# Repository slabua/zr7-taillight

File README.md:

# ZR-7 ATtiny85 Tail Light

###### tags: `SLBLabs` `SLB Labs` `ZR-7` `ZR7` `ZR750` `Kawasaki` `KawasakiZR7` `TailLight` `TailLights` `ATtiny` `ATtiny85` `Arduino` `C/C++`

## A custom motorcycle tail light based on ATtiny85
> Hardware • Firmware • Animations • Automotive-grade considerations

---

## ✦ Overview

The **ZR-7 Tail Light** is a custom-designed motorcycle tail light built around the **ATtiny85** microcontroller.  
It spans the complete stack, from schematic and PCB design to low-level firmware and animation logic, with a focus on robustness, simplicity, and visual clarity.

The goal of this project is not only to function as a tail light, but to serve as a well-engineered embedded system suitable for real automotive environments.

---

## ✦ Features

- ATtiny85-based control logic
- Addressable RGB LED layout
- Distinct operating modes:
  - Tail / running light
  - Brake light
  - Left / right indicators
- Deterministic, non-blocking firmware
- Designed for 12 V motorcycle electrical systems
- Compact, purpose-built PCB

---

## ✦ Hardware

### Core Components

- **MCU:** ATtiny85
- **LEDs:** Addressable RGB LEDs
- **Power:** 12 V input with on-board regulation
- **Inputs:** Brake, left indicator, right indicator

### Design Notes

Several constraints influenced the hardware design:

- **Automotive signal noise**
  Input conditioning and pull-down strategies are used to avoid floating or unstable states.

- **Power integrity**
  The circuit is designed to tolerate voltage fluctuations typical of motorcycle electrical systems.

- **Mechanical constraints**
  PCB shape, connector placement, and LED layout are optimized for the tail light enclosure.

Schematics, PCB layouts, and manufacturing files are included in the `hardware/` directory.

---

## ✦ Firmware

Firmware is written in **C**, targeting the ATtiny85 directly, with no operating system or dynamic memory usage.

### Architecture Highlights

- **State-based rendering**
  Tail, brake, and indicator logic are resolved into a single rendering pipeline.

- **Time-driven animations**
  All animations are non-blocking and tick-based.

- **Config-ready architecture**
  The firmware structure allows future addition of persistent configuration if needed.

Firmware source is located in the `firmware/` directory.

---

## ✦ Build & Flashing

The firmware is developed and flashed using the **Arduino IDE** with an external ISP programmer.

### Requirements

- Arduino IDE
- ATtiny board core (e.g. **ATTinyCore** by Spence Konde)
- Adafruit_NeoPixel library
- ISP programmer:
  - USBtinyISP
  - USBasp

### Arduino IDE Setup

1. Install the ATtiny board package via the Boards Manager.
2. Install the Adafruit_NeoPixel library via the Library Manager.
2. Connect the ISP programmer to the ATtiny85 ISP header.
3. In the Arduino IDE, configure:
   - **Board:** ATtiny85
   - **Clock:** 16.5 MHz
   - **B.O.D Level:** 4.3v
   - **Programmer:** USBtinyISP or USBasp

### Flashing

Use:

``Sketch → Upload Using Programmer``

This compiles the firmware and flashes it directly to the ATtiny85.  
No bootloader is used.

---

## ✦ Media

### PCB details

<details>
  <summary>[More]</summary>

</details>

---

### PCB assembly

<details>
  <summary>[More]</summary>

</details>

---

### Diffuser

<details>
  <summary>[More]</summary>

</details>

---

### Relay

<details>
  <summary>[More]</summary>

</details>

---

- [TODO] Installed tail light images
- [TODO] Short animation demo videos

※ Attached photographs of the assembled PCB are representative of Rev 1.0.

---

## ✦ Repository Layout

```
zr7-taillight/
├── firmware/        # ATtiny85 firmware source
├── hardware/        # Schematics and PCB design
├── docs/            # Images and additional documentation
└── README.md
```

---

## ✦ Safety & Disclaimer

⚠️ **Important Notice**

This project is provided **as-is**, for educational and experimental purposes.

- The author makes **no guarantees** regarding road legality, safety compliance, or fitness for any particular vehicle.
- Modifying vehicle lighting may be regulated or restricted depending on jurisdiction.
- You are solely responsible for ensuring that any implementation complies with **local laws**, **vehicle regulations**, and **safety requirements**.

Use at your own risk.

---

## ✦ Sponsorship

This project is sponsored by **PCBWay**.

PCBWay provided support for PCB manufacturing during the prototyping and validation stages of this project.

It was my first time trying their services and I am pleased with the results.  
The order flow was a little different than what I was used to, but I have been diligently followed thorough the whole process.  
Other than PCB manufacturing, PCBWay also offers services such as CNC and 3D printing. Be sure to check them out at https://www.pcbway.com/

---

## ✦ License

Released under the **MIT License**.
See the `LICENSE` file for details.

---

## ✦ Project Status

The project is **functional and actively evolving**.
Both hardware and firmware are stable, with ongoing refinements and documentation improvements planned.

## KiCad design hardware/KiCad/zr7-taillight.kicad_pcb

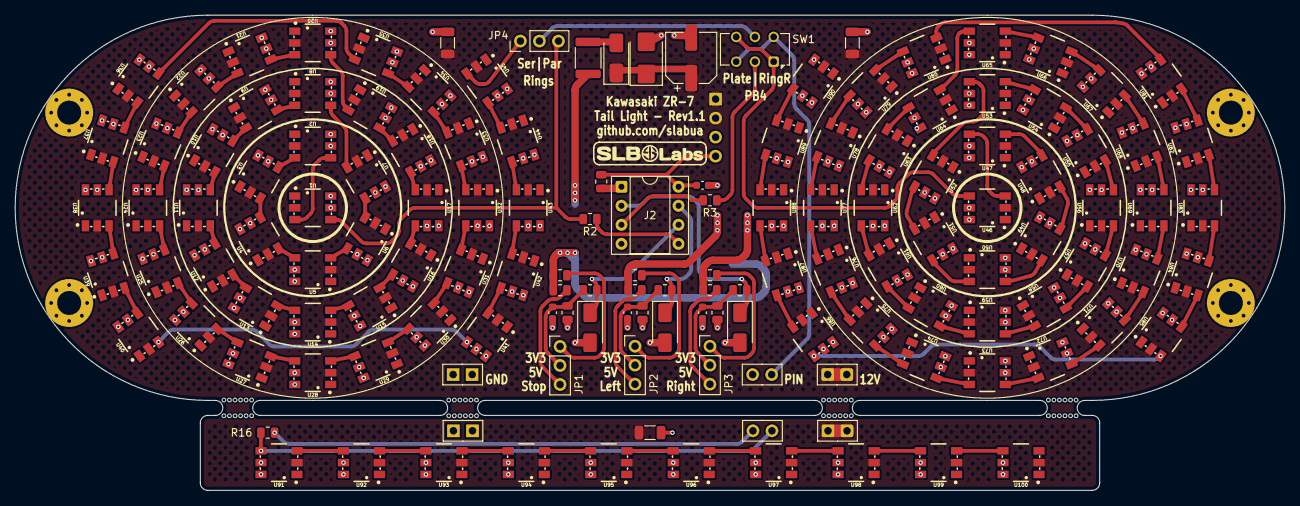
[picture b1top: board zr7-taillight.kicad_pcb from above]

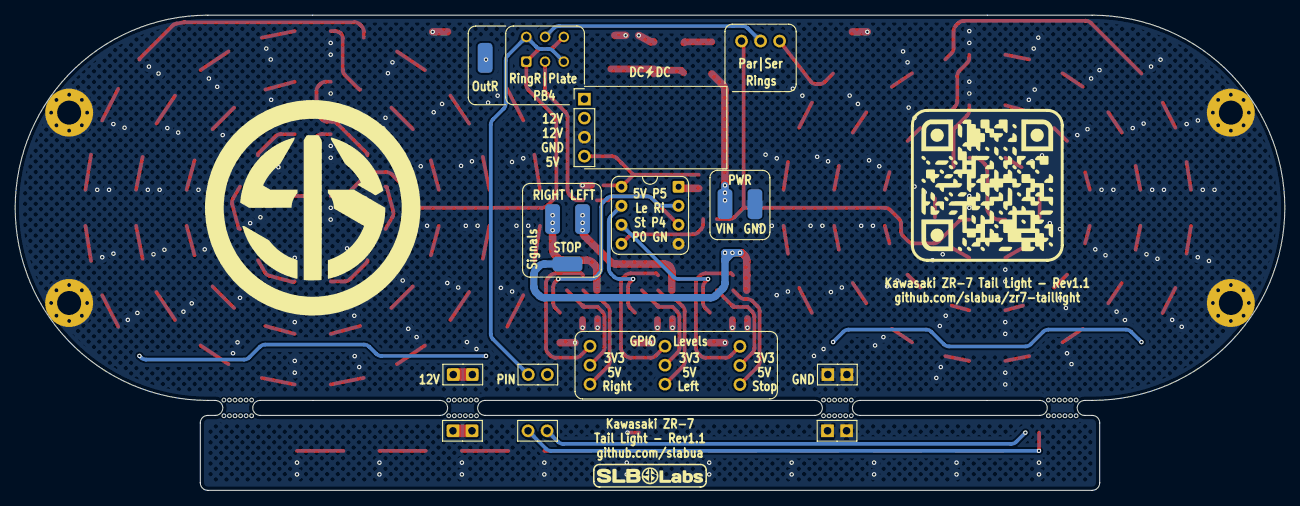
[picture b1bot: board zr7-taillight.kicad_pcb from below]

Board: 2 copper layers, 169.4 x 63.4 mm, 138 parts (2 on the bottom side), 125 nets.

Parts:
C1: 100u; CP_Elec_6.3x5.7
C2, C3, C4, C5: 100n; C_0603_1608Metric
C6, C7, C8: 1u; C_1206_3216Metric
D1: D_Schottky; D_SMA
D2: SMBJ14A; D_SMB
D3, D4, D5: SMAJ5.0A; D_SMA
F1: Polyfuse; SLB-Fuse_1812_4532Metric
J1: Conn_01x04_Pin; SLB-Mini_DCDC
J2: Conn_02x04_Counter_Clockwise; DIP-8_W7.62mm_Socket
JP1, JP2, JP3, JP4: Jumper_3_Open; PinHeader_1x03_P2.54mm_Vertical
R1: 10k; R_0805_2012Metric
R2, R3, R16: 330; R_0805_2012Metric
R4, R5, R6: 1k; R_0805_2012Metric
R7, R8, R9: 4k7; R_0805_2012Metric
R10, R11, R12: 22k; R_0805_2012Metric
R13, R14, R15: 39k; R_0805_2012Metric
Ref**: SLBLabs LOGO only w-border
SW1: SW_DPDT_x2; SW_CK_JS202011CQN_DPDT_Straight
U1, U2, U3, U4, U5, U6, U7, U8, U9, U10, U11, U12, U13, U14, U15, U16, U17, U18, U19, U20, U21, U22, U23, U24, U25, U26, U27, U28, U29, U30, U31, U32, U33, U34, U35, U36, U37, U38, U39, U40, U41, U42, U43, U44, U45, U46, U47, U48, U49, U50, U51, U52, U53, U54, U55, U56, U57, U58, U59, U60, U61, U62, U63, U64, U65, U66, U67, U68, U69, U70, U71, U72, U73, U74, U75, U76, U77, U78, U79, U80, U81, U82, U83, U84, U85, U86, U87, U88, U89, U90, U91, U92, U93, U94, U95, U96, U97, U98, U99, U100: WS2815; LED-TRICOLOR-5050

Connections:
5V: C2.1, J1.4, J2.8, R1.1
12V: C1.1, C6.1, C7.1, C8.1, D1.1 (K), D2.1 (A1), J1.1, J1.2, U1.2 (VDD), U2.2 (VDD), U3.2 (VDD), U4.2 (VDD), U5.2 (VDD), U6.2 (VDD), U7.2 (VDD), U8.2 (VDD), U9.2 (VDD), U10.2 (VDD), U11.2 (VDD), U12.2 (VDD), U13.2 (VDD), U14.2 (VDD), U15.2 (VDD), U16.2 (VDD), U17.2 (VDD), U18.2 (VDD), U19.2 (VDD), U20.2 (VDD), U21.2 (VDD), U22.2 (VDD), U23.2 (VDD), U24.2 (VDD), U25.2 (VDD), U26.2 (VDD), U27.2 (VDD), U28.2 (VDD), U29.2 (VDD), U30.2 (VDD), U31.2 (VDD), U32.2 (VDD), U33.2 (VDD), U34.2 (VDD), U35.2 (VDD), U36.2 (VDD), U37.2 (VDD), U38.2 (VDD), U39.2 (VDD), U40.2 (VDD), U41.2 (VDD), U42.2 (VDD), U43.2 (VDD), U44.2 (VDD), U45.2 (VDD), U46.2 (VDD), U47.2 (VDD), U48.2 (VDD), U49.2 (VDD), U50.2 (VDD), U51.2 (VDD), U52.2 (VDD), U53.2 (VDD), U54.2 (VDD), U55.2 (VDD), U56.2 (VDD), U57.2 (VDD), U58.2 (VDD), U59.2 (VDD), U60.2 (VDD), U61.2 (VDD), U62.2 (VDD), U63.2 (VDD), U64.2 (VDD), U65.2 (VDD), U66.2 (VDD), U67.2 (VDD), U68.2 (VDD), U69.2 (VDD), U70.2 (VDD), U71.2 (VDD), U72.2 (VDD), U73.2 (VDD), U74.2 (VDD), U75.2 (VDD), U76.2 (VDD), U77.2 (VDD), U78.2 (VDD), U79.2 (VDD), U80.2 (VDD), U81.2 (VDD), U82.2 (VDD), U83.2 (VDD), U84.2 (VDD), U85.2 (VDD), U86.2 (VDD), U87.2 (VDD), U88.2 (VDD), U89.2 (VDD), U90.2 (VDD), U91.2 (VDD), U92.2 (VDD), U93.2 (VDD), U94.2 (VDD), U95.2 (VDD), U96.2 (VDD), U97.2 (VDD), U98.2 (VDD), U99.2 (VDD), U100.2 (VDD)
/Left: D4.1 (A1), J2.7, R5.1
/PB5: J2.1, R1.2
/Right: D5.1 (A1), J2.2, R6.1
/Ring_L: J2.5, R2.1
/Ring_R: J2.3, R3.1
/Stop: D3.1 (A1), J2.6, R4.1
GND: C1.2, C2.2, C3.2, C4.2, C5.2, C6.2, C7.2, C8.2, D2.2 (A2), D3.2 (A2), D4.2 (A2), D5.2 (A2), J1.3, J2.4, R7.2, R8.2, R9.2, U1.5 (GND), U1.6 (BIN), U2.5 (GND), U2.6 (BIN), U3.5 (GND), U3.6 (BIN), U4.5 (GND), U4.6 (BIN), U5.5 (GND), U5.6 (BIN), U6.5 (GND), U6.6 (BIN), U7.5 (GND), U7.6 (BIN), U8.5 (GND), U8.6 (BIN), U9.5 (GND), U9.6 (BIN), U10.5 (GND), U10.6 (BIN), U11.5 (GND), U11.6 (BIN), U12.5 (GND), U12.6 (BIN), U13.5 (GND), U13.6 (BIN), U14.5 (GND), U14.6 (BIN), U15.5 (GND), U15.6 (BIN), U16.5 (GND), U16.6 (BIN), U17.5 (GND), U17.6 (BIN), U18.5 (GND), U18.6 (BIN), U19.5 (GND), U19.6 (BIN), U20.5 (GND), U20.6 (BIN), U21.5 (GND), U21.6 (BIN), U22.5 (GND), U22.6 (BIN), U23.5 (GND), U23.6 (BIN), U24.5 (GND), U24.6 (BIN), U25.5 (GND), U25.6 (BIN), U26.5 (GND), U26.6 (BIN), U27.5 (GND), U27.6 (BIN), U28.5 (GND), U28.6 (BIN), U29.5 (GND), U29.6 (BIN), U30.5 (GND), U30.6 (BIN), U31.5 (GND), U31.6 (BIN), U32.5 (GND), U32.6 (BIN), U33.5 (GND), U33.6 (BIN), U34.5 (GND), U34.6 (BIN), U35.5 (GND), U35.6 (BIN), U36.5 (GND), U36.6 (BIN), U37.5 (GND), U37.6 (BIN), U38.5 (GND), U38.6 (BIN), U39.5 (GND), U39.6 (BIN), U40.5 (GND), U40.6 (BIN), U41.5 (GND), U41.6 (BIN), U42.5 (GND), U42.6 (BIN), U43.5 (GND), U43.6 (BIN), U44.5 (GND), U44.6 (BIN), U45.5 (GND), U45.6 (BIN), U46.5 (GND), U46.6 (BIN), U47.5 (GND), U47.6 (BIN), U48.5 (GND), U48.6 (BIN), U49.5 (GND), U49.6 (BIN), U50.5 (GND), U50.6 (BIN), U51.5 (GND), U51.6 (BIN), U52.5 (GND), U52.6 (BIN), U53.5 (GND), U53.6 (BIN), U54.5 (GND), U54.6 (BIN), U55.5 (GND), U55.6 (BIN), U56.5 (GND), U56.6 (BIN), U57.5 (GND), U57.6 (BIN), U58.5 (GND), U58.6 (BIN), U59.5 (GND), U59.6 (BIN), U60.5 (GND), U60.6 (BIN), U61.5 (GND), U61.6 (BIN), U62.5 (GND), U62.6 (BIN), U63.5 (GND), U63.6 (BIN), U64.5 (GND), U64.6 (BIN), U65.5 (GND), U65.6 (BIN), U66.5 (GND), U66.6 (BIN), U67.5 (GND), U67.6 (BIN), U68.5 (GND), U68.6 (BIN), U69.5 (GND), U69.6 (BIN), U70.5 (GND), U70.6 (BIN), U71.5 (GND), U71.6 (BIN), U72.5 (GND), U72.6 (BIN), U73.5 (GND), U73.6 (BIN), U74.5 (GND), U74.6 (BIN), U75.5 (GND), U75.6 (BIN), U76.5 (GND), U76.6 (BIN), U77.5 (GND), U77.6 (BIN), U78.5 (GND), U78.6 (BIN), U79.5 (GND), U79.6 (BIN), U80.5 (GND), U80.6 (BIN), U81.5 (GND), U81.6 (BIN), U82.5 (GND), U82.6 (BIN), U83.5 (GND), U83.6 (BIN), U84.5 (GND), U84.6 (BIN), U85.5 (GND), U85.6 (BIN), U86.5 (GND), U86.6 (BIN), U87.5 (GND), U87.6 (BIN), U88.5 (GND), U88.6 (BIN), U89.5 (GND), U89.6 (BIN), U90.5 (GND), U90.6 (BIN), U91.5 (GND), U91.6 (BIN), U92.5 (GND), U92.6 (BIN), U93.5 (GND), U93.6 (BIN), U94.5 (GND), U94.6 (BIN), U95.5 (GND), U95.6 (BIN), U96.5 (GND), U96.6 (BIN), U97.5 (GND), U97.6 (BIN), U98.5 (GND), U98.6 (BIN), U99.5 (GND), U99.6 (BIN), U100.5 (GND), U100.6 (BIN)
IN_Plate: R16.2, SW1.3 (C), SW1.6 (C), U91.4 (DIN)
IN_Ring_L: JP4.3 (B), R2.2, U1.4 (DIN)
IN_Ring_R: SW1.1 (A), SW1.4 (A), U46.4 (DIN)
LEFT: R11.1, R14.1
unnamed: D1.2 (A), F1.2
unnamed: JP1.1 (A), R13.2
unnamed: JP1.3 (B), R10.2
unnamed: C3.1, JP1.2 (C), R4.2, R7.1
unnamed: JP2.1 (A), R14.2
unnamed: JP2.3 (B), R11.2
unnamed: C4.1, JP2.2 (C), R5.2, R8.1
unnamed: JP3.1 (A), R15.2
unnamed: JP3.3 (B), R12.2
unnamed: C5.1, JP3.2 (C), R6.2, R9.1
unnamed: JP4.2 (C), SW1.5 (B)
unnamed: U1.3 (DO), U2.4 (DIN)
unnamed: U2.3 (DO), U3.4 (DIN)
unnamed: U3.3 (DO), U4.4 (DIN)
unnamed: U4.3 (DO), U5.4 (DIN)
unnamed: U5.3 (DO), U6.4 (DIN)
unnamed: U6.3 (DO), U7.4 (DIN)
unnamed: U7.3 (DO), U8.4 (DIN)
unnamed: U8.3 (DO), U9.4 (DIN)
unnamed: U9.3 (DO), U10.4 (DIN)
unnamed: U10.3 (DO), U11.4 (DIN)
unnamed: U11.3 (DO), U12.4 (DIN)
unnamed: U12.3 (DO), U13.4 (DIN)
unnamed: U13.3 (DO), U14.4 (DIN)
unnamed: U14.3 (DO), U15.4 (DIN)
unnamed: U15.3 (DO), U16.4 (DIN)
unnamed: U16.3 (DO), U17.4 (DIN)
unnamed: U17.3 (DO), U18.4 (DIN)
unnamed: U18.3 (DO), U19.4 (DIN)
unnamed: U19.3 (DO), U20.4 (DIN)
unnamed: U20.3 (DO), U21.4 (DIN)
unnamed: U21.3 (DO), U22.4 (DIN)
unnamed: U22.3 (DO), U23.4 (DIN)
unnamed: U23.3 (DO), U24.4 (DIN)
unnamed: U24.3 (DO), U25.4 (DIN)
unnamed: U25.3 (DO), U26.4 (DIN)
unnamed: U26.3 (DO), U27.4 (DIN)
unnamed: U27.3 (DO), U28.4 (DIN)
unnamed: U28.3 (DO), U29.4 (DIN)
unnamed: U29.3 (DO), U30.4 (DIN)
unnamed: U30.3 (DO), U31.4 (DIN)
unnamed: U31.3 (DO), U32.4 (DIN)
unnamed: U32.3 (DO), U33.4 (DIN)
unnamed: U33.3 (DO), U34.4 (DIN)
unnamed: U34.3 (DO), U35.4 (DIN)
unnamed: U35.3 (DO), U36.4 (DIN)
unnamed: U36.3 (DO), U37.4 (DIN)
unnamed: U37.3 (DO), U38.4 (DIN)
unnamed: U38.3 (DO), U39.4 (DIN)
unnamed: U39.3 (DO), U40.4 (DIN)
unnamed: U40.3 (DO), U41.4 (DIN)
unnamed: U41.3 (DO), U42.4 (DIN)
unnamed: U42.3 (DO), U43.4 (DIN)
unnamed: U43.3 (DO), U44.4 (DIN)
unnamed: U44.3 (DO), U45.4 (DIN)
unnamed: U46.3 (DO), U47.4 (DIN)
unnamed: U47.3 (DO), U48.4 (DIN)
unnamed: U48.3 (DO), U49.4 (DIN)
unnamed: U49.3 (DO), U50.4 (DIN)
unnamed: U50.3 (DO), U51.4 (DIN)
unnamed: U51.3 (DO), U52.4 (DIN)
unnamed: U52.3 (DO), U53.4 (DIN)
unnamed: U53.3 (DO), U54.4 (DIN)
unnamed: U54.3 (DO), U55.4 (DIN)
unnamed: U55.3 (DO), U56.4 (DIN)
unnamed: U56.3 (DO), U57.4 (DIN)
unnamed: U57.3 (DO), U58.4 (DIN)
unnamed: U58.3 (DO), U59.4 (DIN)
unnamed: U59.3 (DO), U60.4 (DIN)
unnamed: U60.3 (DO), U61.4 (DIN)
unnamed: U61.3 (DO), U62.4 (DIN)
unnamed: U62.3 (DO), U63.4 (DIN)
unnamed: U63.3 (DO), U64.4 (DIN)
unnamed: U64.3 (DO), U65.4 (DIN)
unnamed: U65.3 (DO), U66.4 (DIN)
unnamed: U66.3 (DO), U67.4 (DIN)
unnamed: U67.3 (DO), U68.4 (DIN)
unnamed: U68.3 (DO), U69.4 (DIN)
unnamed: U69.3 (DO), U70.4 (DIN)
unnamed: U70.3 (DO), U71.4 (DIN)
unnamed: U71.3 (DO), U72.4 (DIN)
unnamed: U72.3 (DO), U73.4 (DIN)
unnamed: U73.3 (DO), U74.4 (DIN)
unnamed: U74.3 (DO), U75.4 (DIN)
unnamed: U75.3 (DO), U76.4 (DIN)
unnamed: U76.3 (DO), U77.4 (DIN)
unnamed: U77.3 (DO), U78.4 (DIN)
unnamed: U78.3 (DO), U79.4 (DIN)
unnamed: U79.3 (DO), U80.4 (DIN)
unnamed: U80.3 (DO), U81.4 (DIN)
unnamed: U81.3 (DO), U82.4 (DIN)
unnamed: U82.3 (DO), U83.4 (DIN)
unnamed: U83.3 (DO), U84.4 (DIN)
unnamed: U84.3 (DO), U85.4 (DIN)
unnamed: U85.3 (DO), U86.4 (DIN)
unnamed: U86.3 (DO), U87.4 (DIN)
unnamed: U87.3 (DO), U88.4 (DIN)
unnamed: U88.3 (DO), U89.4 (DIN)
unnamed: U89.3 (DO), U90.4 (DIN)
unnamed: U91.3 (DO), U92.4 (DIN)
unnamed: U92.3 (DO), U93.4 (DIN)
unnamed: U93.3 (DO), U94.4 (DIN)
unnamed: U94.3 (DO), U95.4 (DIN)
unnamed: U95.3 (DO), U96.4 (DIN)
unnamed: U96.3 (DO), U97.4 (DIN)
unnamed: U97.3 (DO), U98.4 (DIN)
unnamed: U98.3 (DO), U99.4 (DIN)
unnamed: U99.3 (DO), U100.4 (DIN)
OUT_PB1: R3.2, SW1.2 (B)
OUT_Ring_L: JP4.1 (A), U45.3 (DO)
RIGHT: R12.1, R15.1
STOP: R10.1, R13.1

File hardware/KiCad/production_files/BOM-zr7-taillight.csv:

Comment,Designator,Footprint,LCSC,Quantity
SMAJ5.0A,"D3,D4,D5",D_SMA,C113952,3
100n,"C2,C3,C4,C5",C_0603_1608Metric,C14663,4
SMBJ14A,D2,D_SMB,C152106,1
10k,R1,R_0805_2012Metric,C17414,1
1k,"R4,R5,R6",R_0805_2012Metric,C17513,3
22k,"R10,R11,R12",R_0805_2012Metric,C17560,3
330,"R16,R2,R3",R_0805_2012Metric,C17630,3
4k7,"R7,R8,R9",R_0805_2012Metric,C17673,3
1u,"C6,C7,C8",C_1206_3216Metric,C1848,3
D_Schottky,D1,D_SMA,C22452,1
39k,"R13,R14,R15",R_0805_2012Metric,C25826,3
Polyfuse,F1,SLB-Fuse_1812_4532Metric,C2843993,1
SW_DPDT_x2,SW1,SW_CK_JS202011CQN_DPDT_Straight,C431542,1
100u,C1,CP_Elec_6.3x5.7,C493460,1
Conn_01x04_Pin,J1,SLB-Mini_DCDC,C5116483,1
WS2815,"U1,U10,U100,U11,U12,U13,U14,U15,U16,U17,U18,U19,U2,U20,U21,U22,U23,U24,U25,U26,U27,U28,U29,U3,U30,U31,U32,U33,U34,U35,U36,U37,U38,U39,U4,U40,U41,U42,U43,U44,U45,U46,U47,U48,U49,U5,U50,U51,U52,U53,U54,U55,U56,U57,U58,U59,U6,U60,U61,U62,U63,U64,U65,U66,U67,U68,U69,U7,U70,U71,U72,U73,U74,U75,U76,U77,U78,U79,U8,U80,U81,U82,U83,U84,U85,U86,U87,U88,U89,U9,U90,U91,U92,U93,U94,U95,U96,U97,U98,U99",LED-TRICOLOR-5050,C5446699,100
Conn_02x04_Counter_Clockwise,J2,DIP-8_W7.62mm_Socket,C72129,1

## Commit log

2025-11-30 Add funding info
2026-01-07 Initial commit for the base firmware
2026-01-07 Update to README
2026-01-08 Add KiCad project files
2026-01-08 Update folder structure
2026-01-13 Add current production files
2026-01-13 Minor update to README
2026-01-15 Enhance README with PCB and assembly details
    Added details and images for PCB, assembly, and diffuser sections.
2026-01-15 Enhance README with PCB and assembly details
    Added details about PCB, assembly, and diffuser sections with images.
2026-01-19 Add Relay section to README with images
    Added Relay section with images and details.
2026-01-19 Update Idle/Stop animations
    Add spinning ring via renderSweetTrailEx.
2026-01-20 Update Sweep animation

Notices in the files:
README.md:
License: MIT
